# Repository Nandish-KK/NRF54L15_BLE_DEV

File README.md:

## Overview
This repository contains design files, libraries, and documentation for the NRF BLE transceiver project.
It is **not** an official NRF development board; it is a project I designed as an exercise while learning Altium Designer.

(Renderd with [Blender](https://www.blender.org/) using [*pcb2blender*](https://github.com/30350n/pcb2blender) plugin for KiCAD)

## Things to play around with

- 6-axis IMU (BMI270)
- WS2812 Addressable RGB LED
- Coin cell operation
- Antenna switch for External antenna

## Folder Structure

```text
3D/				  # Contains STEP and Blender files
Altium/           # Altium project files and libraries
Datasheet/        # Datasheets and reference documents
Gerbers/          # Gerbers with PCB constraints optimized for JLCPCB
Pictures/         # Contains Render and Readme pictures
Reference/        # Additional reference layouts and guides
```

## Getting Started

1. Clone the repository:
	```bash
	git clone https://github.com/Nandish-KK/NRF54L15_BLE_DEV
	```
2. Open the Altium project file in `Altium/Nordic_BLE/Nordic_BLE.PrjPcb`.
3. Optionally you can import the Altium project in latest Kicad releases.

## Stackup

JLC04101H-7628

This is a 4-layer stackup with both of the Inner layers being solid ground planes.

## Project Preview

### Schematic

### Top 3D View

### Top Layer

### Bottom Layer

### Bottom 3D View

## Development bugs and fixes
The nrf54 controller comes with `AP_PROTECT` enabled by default. The debuggeres are unable to access the cpu and user flash memory for flashing. In order to unlock the `AP_PROTECT` and get access to the device, the nrf documentation recommends "mass erase". This process will clear the protection registers and allow for flashing.

If your using pyocd inside the nrf-connect terminal with west. During flash it will automatically detect the protection state and will try to erase before flashing. If that doesn't work, try external resets.
```bash
#from the project directory
$ west flash -d build_1/ -r pyocd

# --- OUTPUT ---
-- west flash: rebuilding
[0/5] Performing build step for 'hello_world'
ninja: no work to do.
[4/5] cd /home/user/path/to/project/dir/hello_world/build_1/_sysbuild && /home/user/ncs/toolchains/b2ecd2435d/usr/local/bin/cmake -E true
-- west flash: using runner pyocd
-- runners.pyocd: Flashing file: /media/renri/Hard_disk_Part1/NRF_playground/hello_world/build_1/merged.hex
0000496 W NRF54L15 APPROTECT enabled: will try to unlock via mass erase [target_nRF54L]
0001425 I Loading /home/user/path/to/project/dir/hello_world/build_1/merged.hex [load_cmd]
[==================================================] 100%
0005148 I Erased 36864 bytes (9 sectors), programmed 36864 bytes (9 pages), skipped 0 bytes (0 pages) at 9.75 kB/s [loader]
```

If the protection is enabled, the openenocd 'targets' command will report the main cpu status as unknown as shown below.

```
					 --- Locked State ---
> targets
    TargetName         Type       Endian TapName            State       
--  ------------------ ---------- ------ ------------------ ------------
 0* nrf54l.cpu         cortex_m   little nrf54l.cpu         unknown
 1  nrf54l.aux         mem_ap     little nrf54l.cpu         running

					--- Unlocked State ---
 > targets
    TargetName         Type       Endian TapName            State       
--  ------------------ ---------- ------ ------------------ ------------
 0* nrf54l.cpu         cortex_m   little nrf54l.cpu         running
 1  nrf54l.aux         mem_ap     little nrf54l.cpu         running
````

You can use the following pyocd commands to erase the chip. Although you can connect via openocd, there doesn't seem to be a relibale way to erase the chip with `AP_PROTECT` enabled.
Use the pyocd provided along with the nrf connect or install the latest version of pyocd if you prefere to use it externally. 

```bash
$ pyocd erase --mass --target nrf54l

# --- OUTPUT ---
0000395 W NRF54L15 is not in a secure state [target_nRF54L]
0000608 I Mass erasing device... [eraser]
0001324 I Mass erase complete [eraser]

```
If pyocd command fails to erase/flash with cmsis debugger, try power cycling.

[Working with the nRF52 Series' improved APPROTECT](https://devzone.nordicsemi.com/nordic/nordic-blog/b/blog/posts/working-with-the-nrf52-series-improved-approtect). 

Currently, I don't have J-link at hand. This meant I had to do quite a bit of detective work to come up with a solution. I found the solution in the seedstudio forum discussion on Xiao-nrf54l15. The discussion provides quite a bit of insight on the issues that you might face.
[Xiao-nrf54l15 Memory transfer fault](https://forum.seeedstudio.com/t/xiao-nrf54l15-an-error-occurred-memory-transfer-fault-0x00ffc31c-0x00ffc31f/293792/26?page=2)
[Control access port protection documentation]

## Design Notes

* Hold the Boot button for uploading the CMSIS-DAP firmware for CH552 (first time only)
* Use the toggle switch to select the USB or Coin-cell operation
* The Antenna switch is powered with the GPIO _P1.09 and is controlled by GPIO P1.10; configure GPIOs for proper RF operation.
* Every GPIO used onboard has a bridger solder link. If any project requires these GPIOs externally, simply cut the closed solder bridge trace.

## On-Board Debugger

The Board design utilizes a CH552P microcontroller with a CMSIS-DAP firmware as a built-in debugger for NRF microcontroller. The CH552P is opted mainly due to its low cost and smaller footprint.
If you are designing your own board and would like to have a micro that is available at sites like digikey, mouser etc, then consider the SAMD11 series from microchip. These are fairly optimized for cost and size.

```
This project uses the Debugger implementation from wagiminator's CH552-DAPLink project.
Check out his project at: 

> github.com/wagiminator/CH552-DAPLink
> oshwlab.com/wagiminator/ch552g-daplink

```

## License
This work is licensed under CC BY-SA 4.0.
(https://creativecommons.org/licenses/by-sa/4.0/)

---

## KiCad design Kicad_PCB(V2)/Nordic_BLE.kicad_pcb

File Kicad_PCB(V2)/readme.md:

#Rev 2 changes
- swapped RGB led gpio 
- Increased board dimension to account for better T-line design, testing and implement a pi matching network.

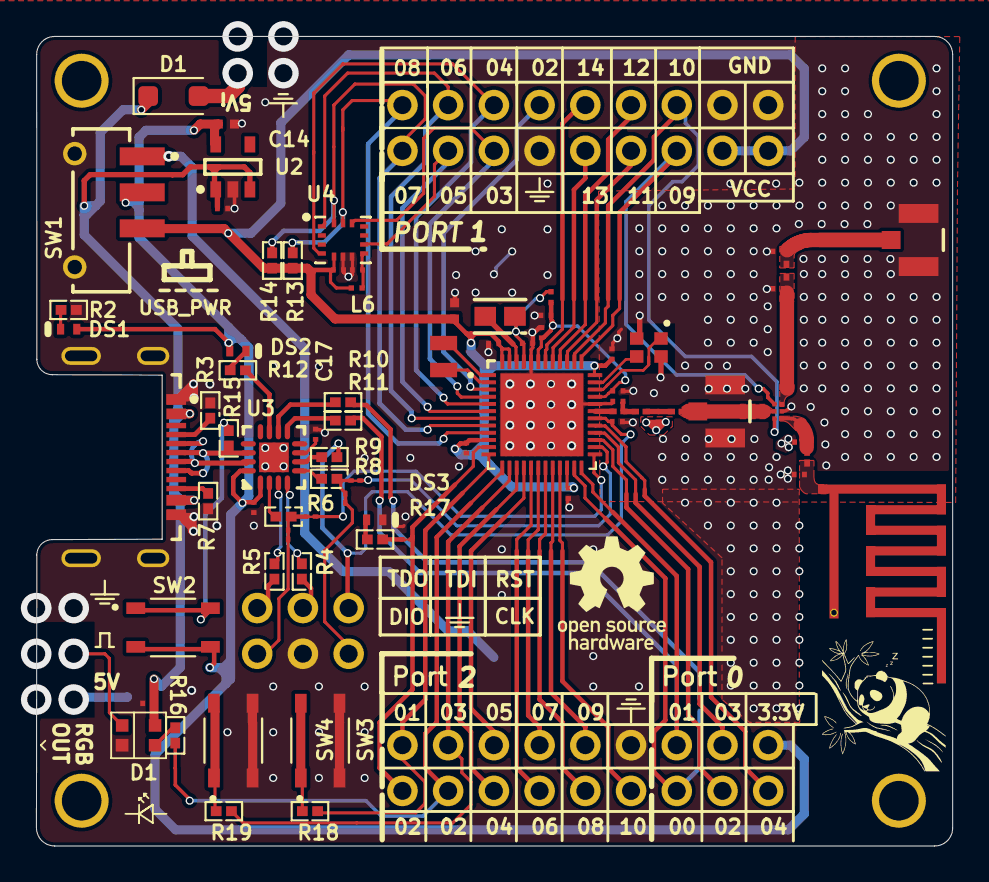
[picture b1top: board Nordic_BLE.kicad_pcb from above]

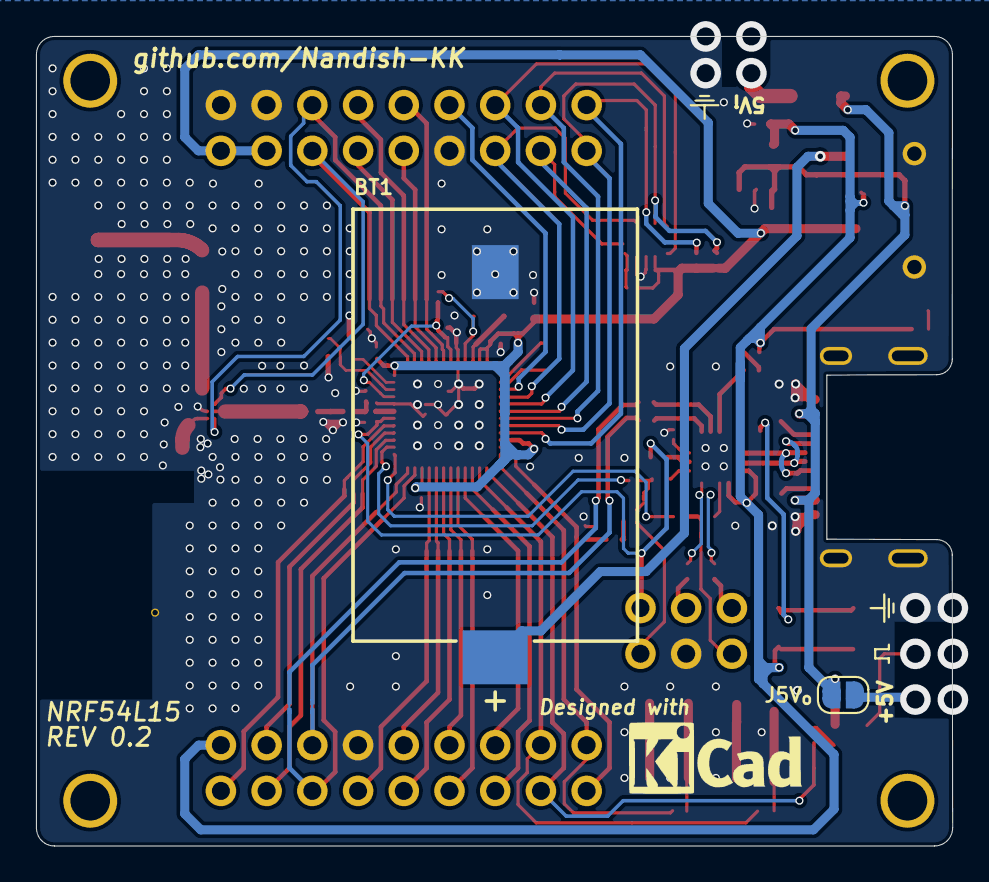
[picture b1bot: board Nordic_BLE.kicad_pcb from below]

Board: 4 copper layers, 50.9 x 45.0 mm, 124 parts (4 on the bottom side), 82 nets.

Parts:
A1: 2.4GHz MIFA Antenna; 2.4GHZ MIFA
BT1: S8421-45R; FP-S8421-45R-MFG
C1: 10uF; 0402_SMD_CAPACITOR
C2, C3, C4, C5, C15, C16, C18, C19, C20: 100nF; 0201 SMD CAPACITOR
C6, C10: 2.2uF; 0201 SMD CAPACITOR
C7: 1.5pF; 0201 SMD CAPACITOR
C8: 2.0pF; 0201 SMD CAPACITOR
C11: 10nF; 0201 SMD CAPACITOR
C12: 2.2nF; 0201 SMD CAPACITOR
C13, C17: 3.9pF; 0201 SMD CAPACITOR
C14: 1uF; 0402_SMD_CAPACITOR
C21, C21#2, C22, C22#2: DNP; 0201 SMD Capacitor
D1: D_SOD-123F
D1#2: WS2812B-2020
DS1, DS2, DS3: 16-219A/T2D-AR2T1QY/3T; EVRL-0402-2_V
J1, J2, J3, J4, J5, J6, J7, J8, J9, J10, J11, J12, J13, J14, J15, J16, J17, J18, J19, J20, J21, J22, J23, J24, J25, J26, J27, J28, J29, J30, J31, J32, J33, J34, J35, J36, J47, J48, J49, J50, J51, J52: Single_Header_2.54mm; SINGLE_HEADER_2.54MM
J1_USB: 216990-0002; FP-216990-0002-MFG
J5V_{o}: SolderJumper-2_P1.3mm_Open_RoundedPad1.0x1.5mm
J43, J53, J54, J57, J58: Shorted_Solder_Bridge; SHORTED_SOLDER_BRIDGE
J55, J56: Open_Solder_Bridge; OPEN_SOLDER_BRIDGE
J59, J59#2: U.FL-R-SMT(10); FP-U_FL-R-SMT_10-MFG
L1: 4.7uH; FP-MLZ1608-IPC_A
L2: 2.7nH; 0201_SMD_INDUCTOR
L3, L4: 3.5nH; 0201_SMD_INDUCTOR
L5, L6: FB1; 0201_SMD_INDUCTOR
L7, L8: DNP; 0201_SMD_INDUCTOR
M1, M2, M3, M4: M2_Mounting_Hole; M2 MOUNTING HOLE
R2, R12, R17: 1k; RES_0402_GENERIC
R3, R7: 5.1k; RES_0402_GENERIC
R4, R5, R6, R8, R9, R10, R11, R16: 100R; RES_0402_GENERIC
R13, R14: 100k; RES_0402_GENERIC
R15, R18, R19: 10k; RES_0402_GENERIC
SW1: CSS-1210TB; FP-CSS-1210TB-MFG
SW2, SW3, SW4: SKRPABE010; SW_SKRPABE010
U1: NRF54L15-QFAA-R Split Symbol; NRF54L15_LQFN_48
U2: TCR2EF33; TCR2EF33-SOT-23-5
U3: CH552P-QFN16; CH552-QFN16_3X3
U4: BMI270_IMU; BMI_270_PQFN50P300X250X70-14L
U5: BGS12P2L6E6327XTSA1; FP-PG-TSLP-6-MFG
Y1: 32MHz; OSC_XRCGB32M000F2P01R0
Y2: CM8V-T1A-32.768KHZ-9PF-20PPM-TA-QC; XTAL_CM8V-T1A-32.768KHZ-9PF-20PPM-TA-QC

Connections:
3V: BT1.2, SW1.1
+5V: C15.2, C20.2, D1.1, D1#2.4, J1_USB.A4-B9, J1_USB.B4-A9, J5V_{o}.2, U2.1, U2.3
ANT: L2.1, U1.31
CLK: J53.2, J55.2, R8.2
DAP_USB_N: J1_USB.A7, J1_USB.B7, U3.15
DAP_USB_P: J1_USB.A6, J1_USB.B6, R15.1, U3.14
DCC: L1.2, U1.46
DEBUG_RX: R10.1, U3.10
DEBUG_TX: R11.2, U3.9
DECA: C10.2, C11.2, C12.2, L5.1, U1.33, U1.43
DECD: C6.2, L1.1, L5.2, U1.45
DIO: J54.2, J56.2, R6.2
GND: A1.2, BT1.1, C1.1, C2.1, C3.1, C4.1, C5.1, C6.1, C7.1, C8.1, C10.1, C11.1, C12.1, C13.1, C14.1, C15.1, C16.1, C17.1, C18.1, C19.1, C20.1, C21.1, C21#2.1, C22.1, C22#2.1, D1#2.2, DS3.2, J1_USB.1, J1_USB.2, J1_USB.3, J1_USB.4, J1_USB.A1-B12, J1_USB.B1-A12, J18.1, J19.1, J35.1, J36.1, J50.1, J59.2, J59.3, J59#2.2, J59#2.3, R2.1, R3.1, R7.1, SW1.4, SW1.5, SW3.3, SW3.4, SW4.3, SW4.4, U1.32, U1.44, U1.49, U2.2, U3.17, U4.6, U4.7, U5.2, Y1.2, Y1.4
NetC7_2: C7.2, L2.2, L3.1
NetC8_2: C8.2, L3.2, L4.1
NetC17_2: C17.2, U3.7
NetD1_3: D1#2.3, R16.2
NetDS1_2: DS1.2, R2.2
NetDS2_2: DS2.2, R12.2
NetDS3_1: DS3.1, R17.1
NetJ1_USB_A5: J1_USB.A5, R3.2
NetJ1_USB_B5: J1_USB.B5, R7.2
NetJ43_2: J43.2, R17.2
NetJ48_1: J48.1, J55.1
NetJ52_1: J52.1, J56.1
NetJ53_1: J53.1, U1.26
NetJ54_1: J54.1, U1.25
NetJ57_2: J57.2, R10.2
NetJ58_2: J58.2, R11.1
NetL7_1: C21.2, L7.1, U5.3
NetL8_1: C22.2, L8.1, U5.1
NetR4_1: R4.1, U3.4
NetR5_1: R5.1, U3.3
NetR6_1: R6.1, U3.2
NetR8_1: R8.1, U3.5
NetR9_1: R9.1, U3.6
NetR12_1: R12.1, U3.11
NetR15_2: R15.2, SW2.1, SW2.2
NetR18_1: R18.1, SW3.1, SW3.2
NetR19_1: R19.1, SW4.1, SW4.2
NetU1_1: U1.1, Y2.2
NetU1_2: U1.2, Y2.1
P0.02: J25.1, U1.27
P0.03: J28.1, U1.28
P0.04: J30.1, U1.29
P1.02: J1.1, U1.3
P1.03: J3.1, U1.4, U4.12
P1.04: J5.1, U1.5, U4.4
P1.05: J7.1, U1.6, U4.9
P1.06: J9.1, U1.7, U4.1
P1.07: J11.1, R14.1, U1.8, U4.14
P1.08: J13.1, R13.1, U1.9, U4.13
P1.09: J15.1, U1.37, U5.4
P1.10: J20.1, U1.38, U5.6
P1.11: J23.1, U1.39
P1.12: J26.1, U1.40
P1.13: J29.1, U1.41
P1.14: J31.1, U1.42
P2.00: J2.1, J43.1, U1.11
P2.01: J4.1, R18.2, U1.12
P2.02: J6.1, R16.1, U1.13
P2.03: J8.1, R19.2, U1.14
P2.04: J10.1, U1.15
P2.05: J12.1, U1.16
P2.06: J14.1, U1.17
P2.07: J16.1, U1.18
P2.08: J21.1, U1.19
P2.09: J24.1, U1.20
P2.10: J27.1, U1.21
RF_Co-ax: C21#2.2, J59.1, L7.2
RF_IFA: A1.1, C22#2.2, L8.2
RF_OUT: J59#2.1, L4.2, U5.5
RST: C13.2, J51.1, R9.2, U1.30
TDI: J47.1, R4.2
TDO: J49.1, R5.2
UART_RX: J22.1, J58.1, U1.24
UART_TX: J17.1, J57.1, U1.23
VCC_nRF: C1.2, C2.2, C3.2, C4.2, C5.2, C18.2, J32.1, J34.1, L6.2, R13.2, R14.2, SW1.3, U1.10, U1.22, U1.36, U1.47, U1.48, U4.5
VDD_3V3: C14.2, C16.2, DS1.1, DS2.1, J33.1, SW1.2, SW2.3, SW2.4, U2.5, U3.1, U3.16
VDD_A: C19.2, L6.1, U4.8
XC1: U1.34, Y1.1
XC2: U1.35, Y1.3

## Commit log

2025-10-22 Added 3D folder and updated Readme
2025-12-04 Added Software folder
2025-12-04 edited Readme
2026-01-20 Rename Readme.md to README.md
2026-06-10 Added V2 Kicad PCB and removed VNA results folder
2026-06-10 updated readme, examples and added V2
